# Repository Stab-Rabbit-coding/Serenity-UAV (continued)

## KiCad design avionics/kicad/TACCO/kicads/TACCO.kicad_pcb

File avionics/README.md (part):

# Serenity UAV — Avionics Subsystem

**License:** CC BY-SA 4.0 — creativecommons.org/licenses/by-sa/4.0 (SPDX-License-Identifier: CC-BY-SA-4.0)
see [License](#license) below.  
**Current design revision:** tracked per board, not subsystem-wide — see "PCB Boards" below and
each board's own `avionics/kicad/<board>/<board>.md` status file for its current revision and
sch↔PCB parity state. `avionics/WBS.md` carries the subsystem-wide work breakdown (no changelog
section number is stable enough to cite here; search the file instead of citing a section).

> Avionics subsystem for the Serenity UAV: 8-node cooperative flight control,
> PACE failover architecture, EMI-hardened PCBs, multi-link comms (CAN FD, RS-485,
> Ethernet, MIL-STD-1553C, 49 MHz / SiK / mLRS), and signed telemetry logging with
> hardware-enforced write protection.

## Current Status (2026-10-07)

The design revision is Rev T. Hardware is in PCB layout; nothing is fabricated yet.

| Item | State |
|------|-------|
| Pilot | Schematic and PCB generated together; ERC 0, DRC 0, parity 0; 120 of 120 parts placed; **routing and Gerbers open** |
| TACCO | 163 parts placed on a 60 × 35 mm outline; ERC 0, DRC 0, parity 0 before routing; **routing, Gerbers, and USB Wi-Fi module selection (fab blocker) open** |
| PB2 rails (Pilot, TACCO) | Corrected 2026-10-05/06 to 4.80 mm from each long edge on Samtec TSM-118-04-L-DV-LC male strips; the earlier 2.54 mm placement could not mate with the PB2-I |
| Fleet 1553C | Holt HI-6138 protocol engine on Pilot and TACCO (decision 2026-09-28) |
| Flight Engineer | ERC 0; 29–31 DRC items open; not routed |
| Commo | Rev T standalone bus node approved 2026-09-29; Rev S cape design superseded; Rev T schematic and PCB in design |
| Observer | Schematic ahead of PCB; PCB resync not started (124 DRC) |
| Bus-Gateway | `N_STACKS=4` generated; about 84% routed; 1 DRC item |
| Encoder | Schematic, PCB, ERC 0, DRC 0; bench calibration open |
| Firmware | `serenity-cn` Phase 6 done; `serenity-fc` Phase 6 stub; Phase 7 open (`firmware/WBS.md`) |

Per-board detail: `kicad/README.md` and each board's `.md` file. Open work: `TODO.md`.

## Architecture Overview

**8-Node PACE Failover System** (Primary / Alternative / Contingency / Emergency):

| Stack | Watchdog | Comms | Flight Control | Payload |
|-------|----------|-------|----------------|---------|
| Shepherd (Bay A) | P | A | C | E |
| Inara (Bay B) | A | P | E | C |
| River (Bay C) | C | E | P | A |
| Simon (Bay D) | A | C | A | P |

Each node runs a **PocketBeagle2 Industrial (PB2-I) SBC** carrying:

- **Pilot** cape: flight control + sensor interface (Cape-A-2)
- **TACCO** cape: comms/logging/payload interface (Cape-B-2). "XO" is a legacy/internal working
  name still present in some script and file names (e.g. `gen_xo_sch.py`) — TACCO is the
  canonical current name; see `avionics/AGENTS.md` "Cape Naming and Revision History."
- **Commo** (49 MHz + SiK transceivers). Rev S was a PB2-I cape in River's Room (Bay C) and
  Simon's Medbay (Bay D). **Rev T (approved 2026-09-29)** replaces both with one standalone
  MCU node at the antennas, reachable by all four stacks; see `avionics/AGENTS.md`.

**Flight Engineer** (Power Distribution Board) sits in the middle-section inner neck, minimizing
power-run length to all four nacelles and the battery.

**Observer** (standalone vision/ToF/laser board — not a PB2-I cape) installs at the nose and
cargo-bay mounting sites, connected via the Ethernet ring and CAN FD trunk. It shares the
Ethernet ring with the 8 PACE nodes but is not itself one of them, so the ring's actual physical
node count exceeds 8 — see `avionics/AGENTS.md` and `avionics/kicad/Observer/Observer.md`.

**Bus-Gateway** (CAN-PERIPH-GW-1) is a secure CAN-FD/RS-485 edge node that brings bus connectivity
to sensors/actuators that lack it natively — nacelle tilt Hall-effect encoders, SG90
micro-servos (winch, cargo door), and per-EDF ESC telemetry. It is deployed in multiple physical
instances (per-nacelle encoder gateway, per-EDF ESC gateway, cargo-door servo gateway); see
`avionics/kicad/Bus-Gateway/CAN-PERIPH-GW-1.md`. The Pilot/TACCO README bullets below describe
these signals as if read/driven locally; several have since moved to bus-networked control
through Bus-Gateway — check the per-board `.md` files for current wiring before assuming a
local GPIO/analog connection.

**Encoder** (ENC-NACELLE-1) is the nacelle tilt-angle sensor PCB (AK7455 off-axis magnetoresistive
encoder); it now reports over CAN-FD/RS-485 through Bus-Gateway rather than being read directly
by Pilot — see `avionics/kicad/Encoder/ENC-NACELLE-1.md`.

## Onboard Bus Architecture

| Bus | Protocol | Nodes | Purpose |
|-----|----------|-------|---------|
| CAN FD | 1 Mbps nominal / 8 Mbps data | 8 PACE nodes + Bus-Gateway instances + Observer + Commo (Rev T) + Flight Engineer | Primary telemetry, ESC heartbeat, sensor fusion, failover signaling |
| RS-485 | Half-duplex | 8 PACE nodes + Bus-Gateway instances + Commo (Rev T) + Flight Engineer | Backup command/telemetry (fallback if CAN FD fails) |
| Ethernet | RSTP ring | 8 PACE nodes (via Pilot's dual PHYs, J_ETH1/J_ETH2) + Observer | High-bandwidth sensor data, inter-node video/imaging streams |
| MIL-STD-1553C | Dual redundant buses | 8 PACE nodes + Commo (Rev T) as a remote terminal | Deterministic real-time control; Holt HI-6138 protocol engine on every Pilot and TACCO |
| UART | Various | Cape headers | Serial debugging, bootloader, optional mission-specific sensors |

## External Comms (5 Independent Paths)

All five paths are **authenticated, signed, logged**. Every stack's TACCO cape carries Wi-Fi,
ZigBee, and mLRS. Under Rev S only River and Simon carried a Commo cape (49 MHz + SiK); under
Rev T every stack reaches the one standalone Commo node over the bus. See root `AGENTS.md` §9 for
the per-stack primary/secondary assignment.

1. **Wi-Fi 5 GHz** — MAVLink to QGroundControl; primary for higher-bandwidth development
   flights; range limited (<500 m line-of-sight); all 4 stacks (TACCO). Host interface moved to a
   USB module on the PB2's USB1 (the SDIO bus is not on the PB2 headers); module selection is open
2. **ZigBee 2.4 GHz** — MAVLink fallback; robust link in congested RF environments; all 4 stacks
   (TACCO, Murata Type 2EL module; 802.15.4 is hosted on SPI0)
3. **mLRS (bare ST STM32WLE5JC)** — LoRa-class long-range link; all 4 stacks (TACCO). Replaced
   the Seeed Wio-E5 module on 2026-09-29 (restricted-country sourcing rule); RF matching values
   need bench tuning before flight. Replaced TACCO's SiK radio in the 2026-09-21 relocation and
   is the long-range fallback if the single Commo node is lost
4. **MAVLink/SiK 915 MHz** — Licensed ISM band; range ~5 km (open field, typical line-of-sight);
   via Commo (RFD900ux-SMT) — moved there from TACCO in the 2026-09-21 relocation. Rev S: River
   and Simon only; Rev T: all stacks
5. **49 MHz (Part 15 §15.235)** — Unlicensed, extremely low power (~30 µW EIRP); via Commo (Rev S: River and
   Simon only; Rev T: all stacks); forward and aft wire antennas (see `XCVR-49MHZ` in BOM); carries
   encrypted command/telemetry; requires FCC pre-compliance (energy-limited but not
   power-limited per Part 15)

## PCB Boards

Board revisions, sch↔PCB parity, ERC/DRC status, and exact IC/rail specs move fast and are
tracked at the source — each board's own `avionics/kicad/<board>/<board>.md`, cross-referenced
from `avionics/TODO.md` §1.2. The summaries below are architectural (what the board does, not
its exact current bring-up state); confirm specifics against the per-board `.md` before relying
on them for fab, BOM, or integration decisions.

### Pilot (Cape-A-2) — Flight Control + Sensors

- **Processor:** PocketBeagle2 Industrial (Cortex-A53, dual PRU real-time subsystem)
- **Sensors:** 9-DOF IMU, barometric altimeter, GPS (u-blox M10Q)
- **Motor Control:** 4× PWM outputs (ESC1–4) for nacelle EDFs; isolated gate drivers
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
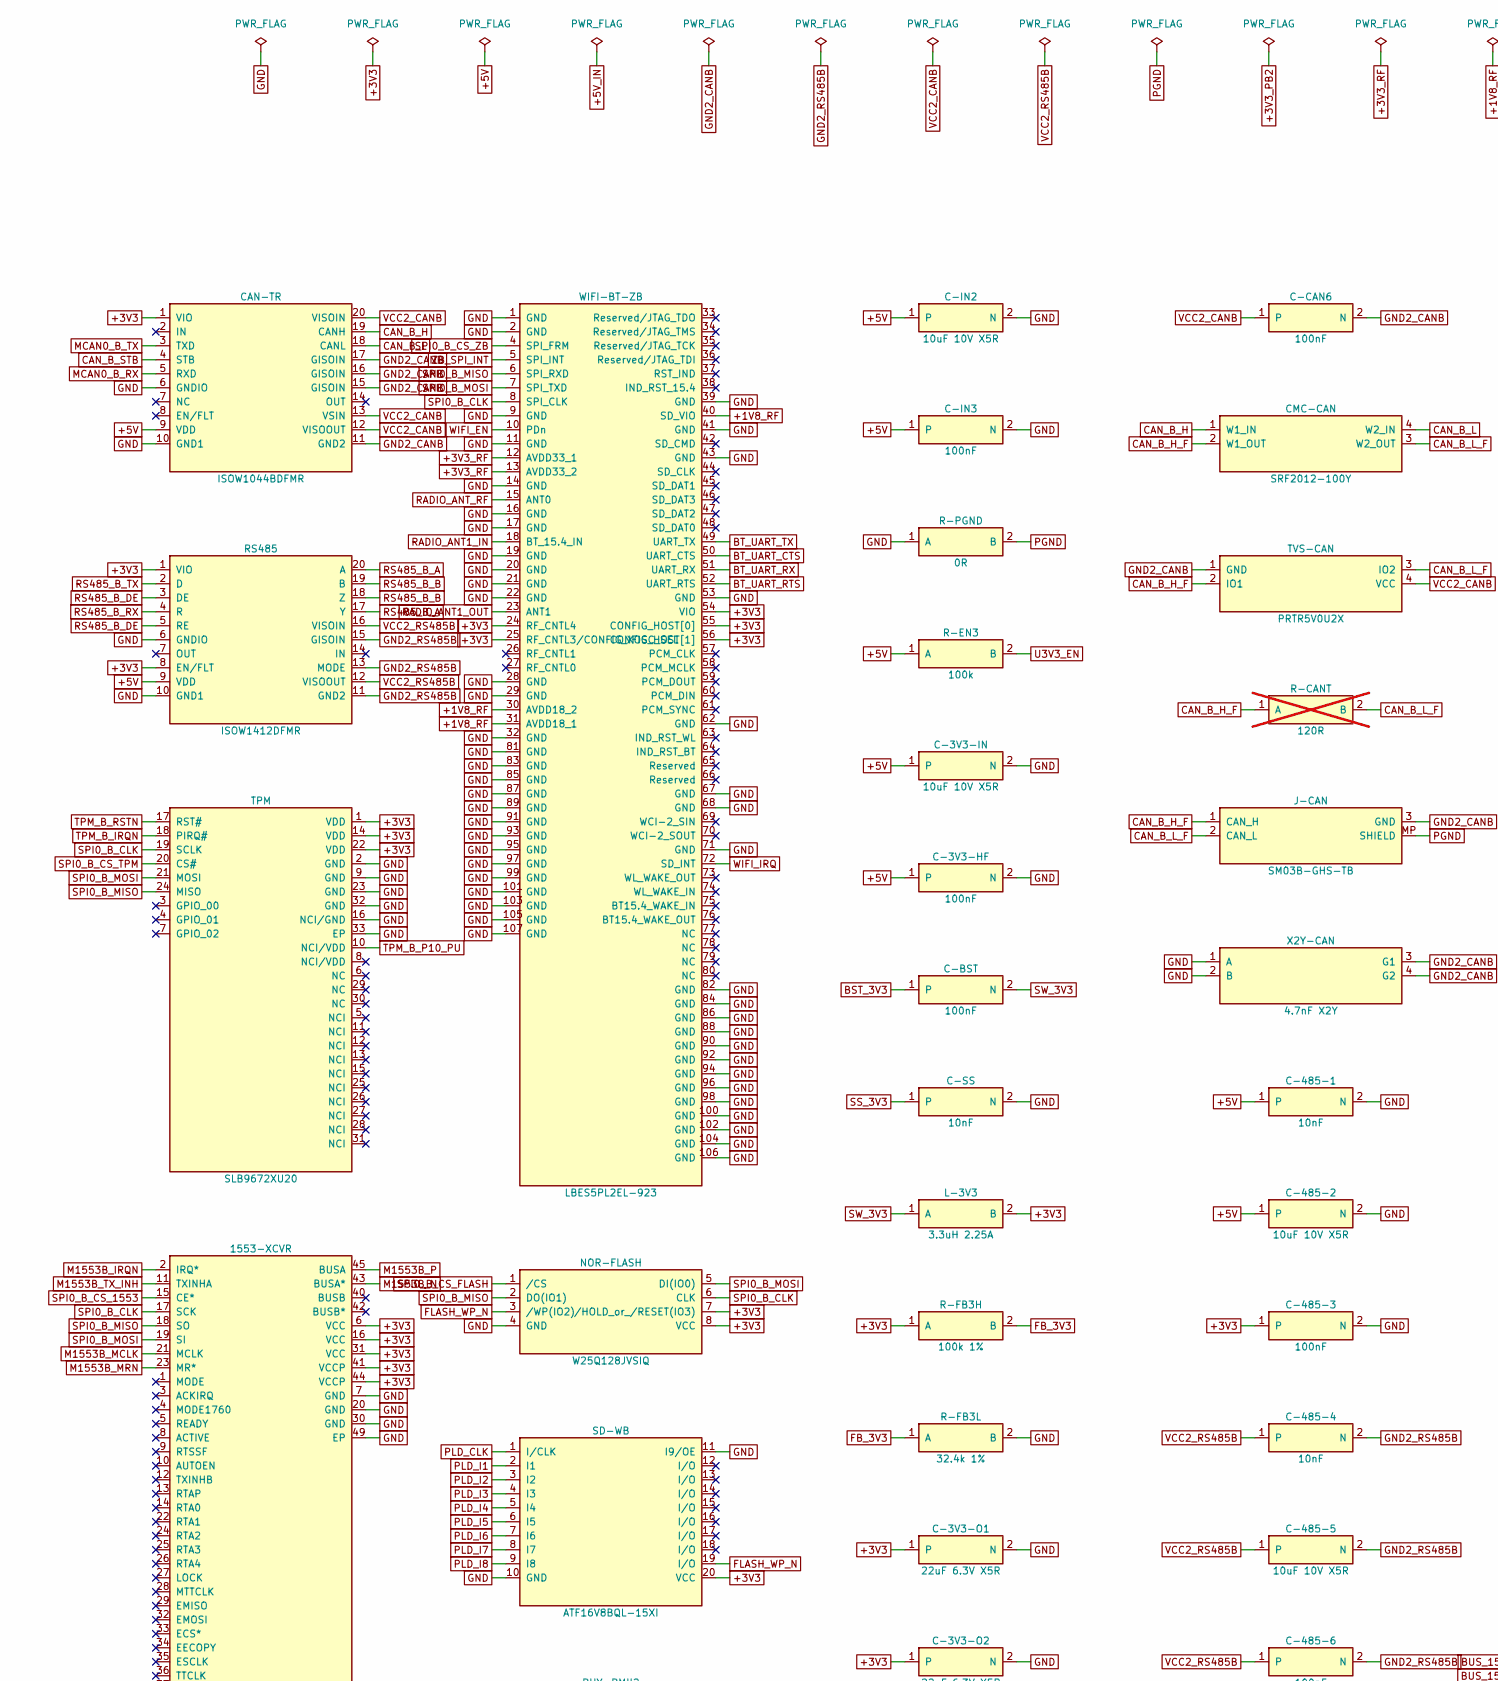
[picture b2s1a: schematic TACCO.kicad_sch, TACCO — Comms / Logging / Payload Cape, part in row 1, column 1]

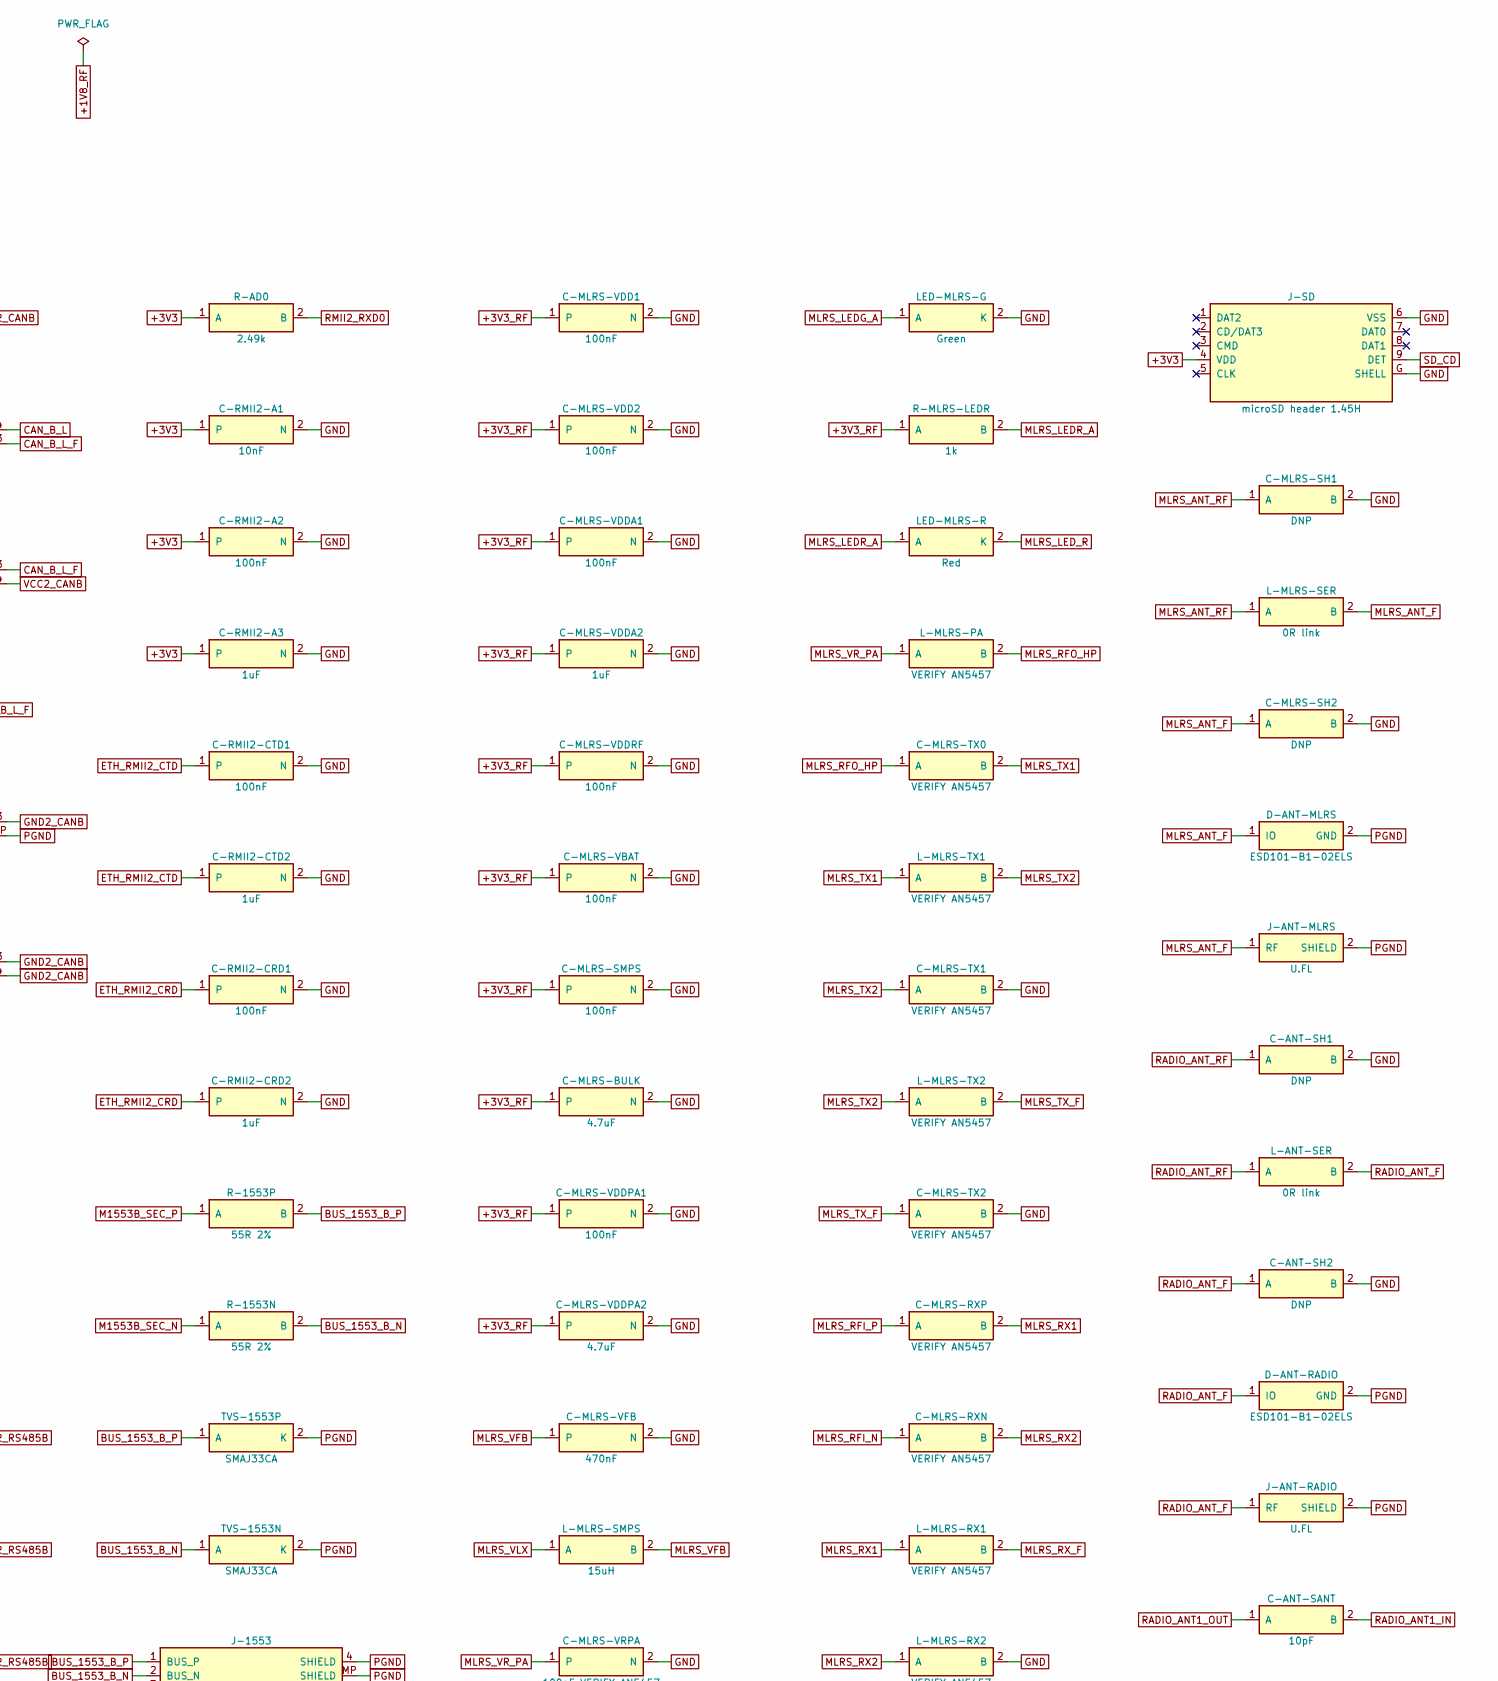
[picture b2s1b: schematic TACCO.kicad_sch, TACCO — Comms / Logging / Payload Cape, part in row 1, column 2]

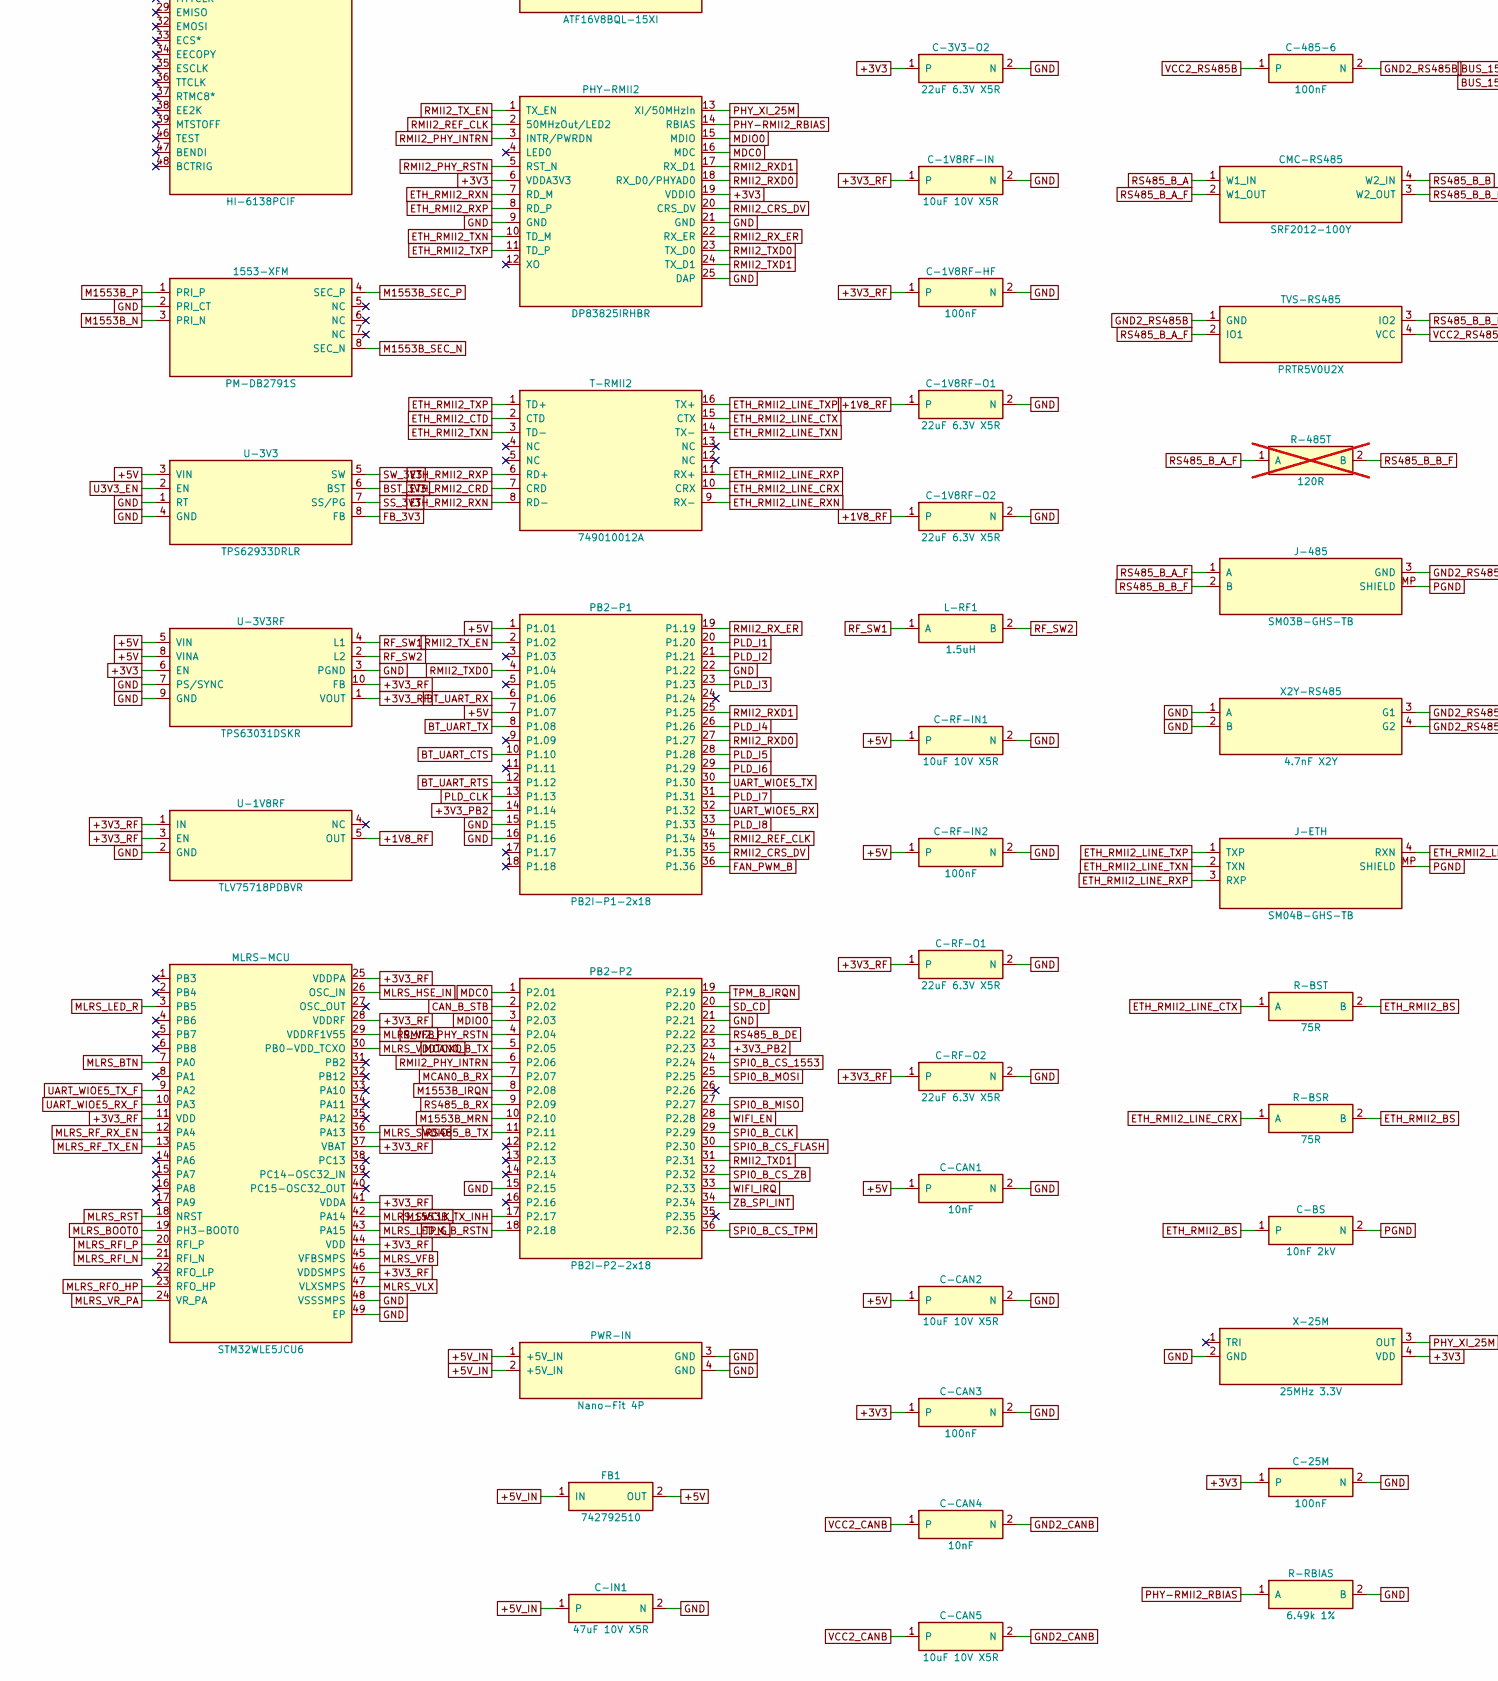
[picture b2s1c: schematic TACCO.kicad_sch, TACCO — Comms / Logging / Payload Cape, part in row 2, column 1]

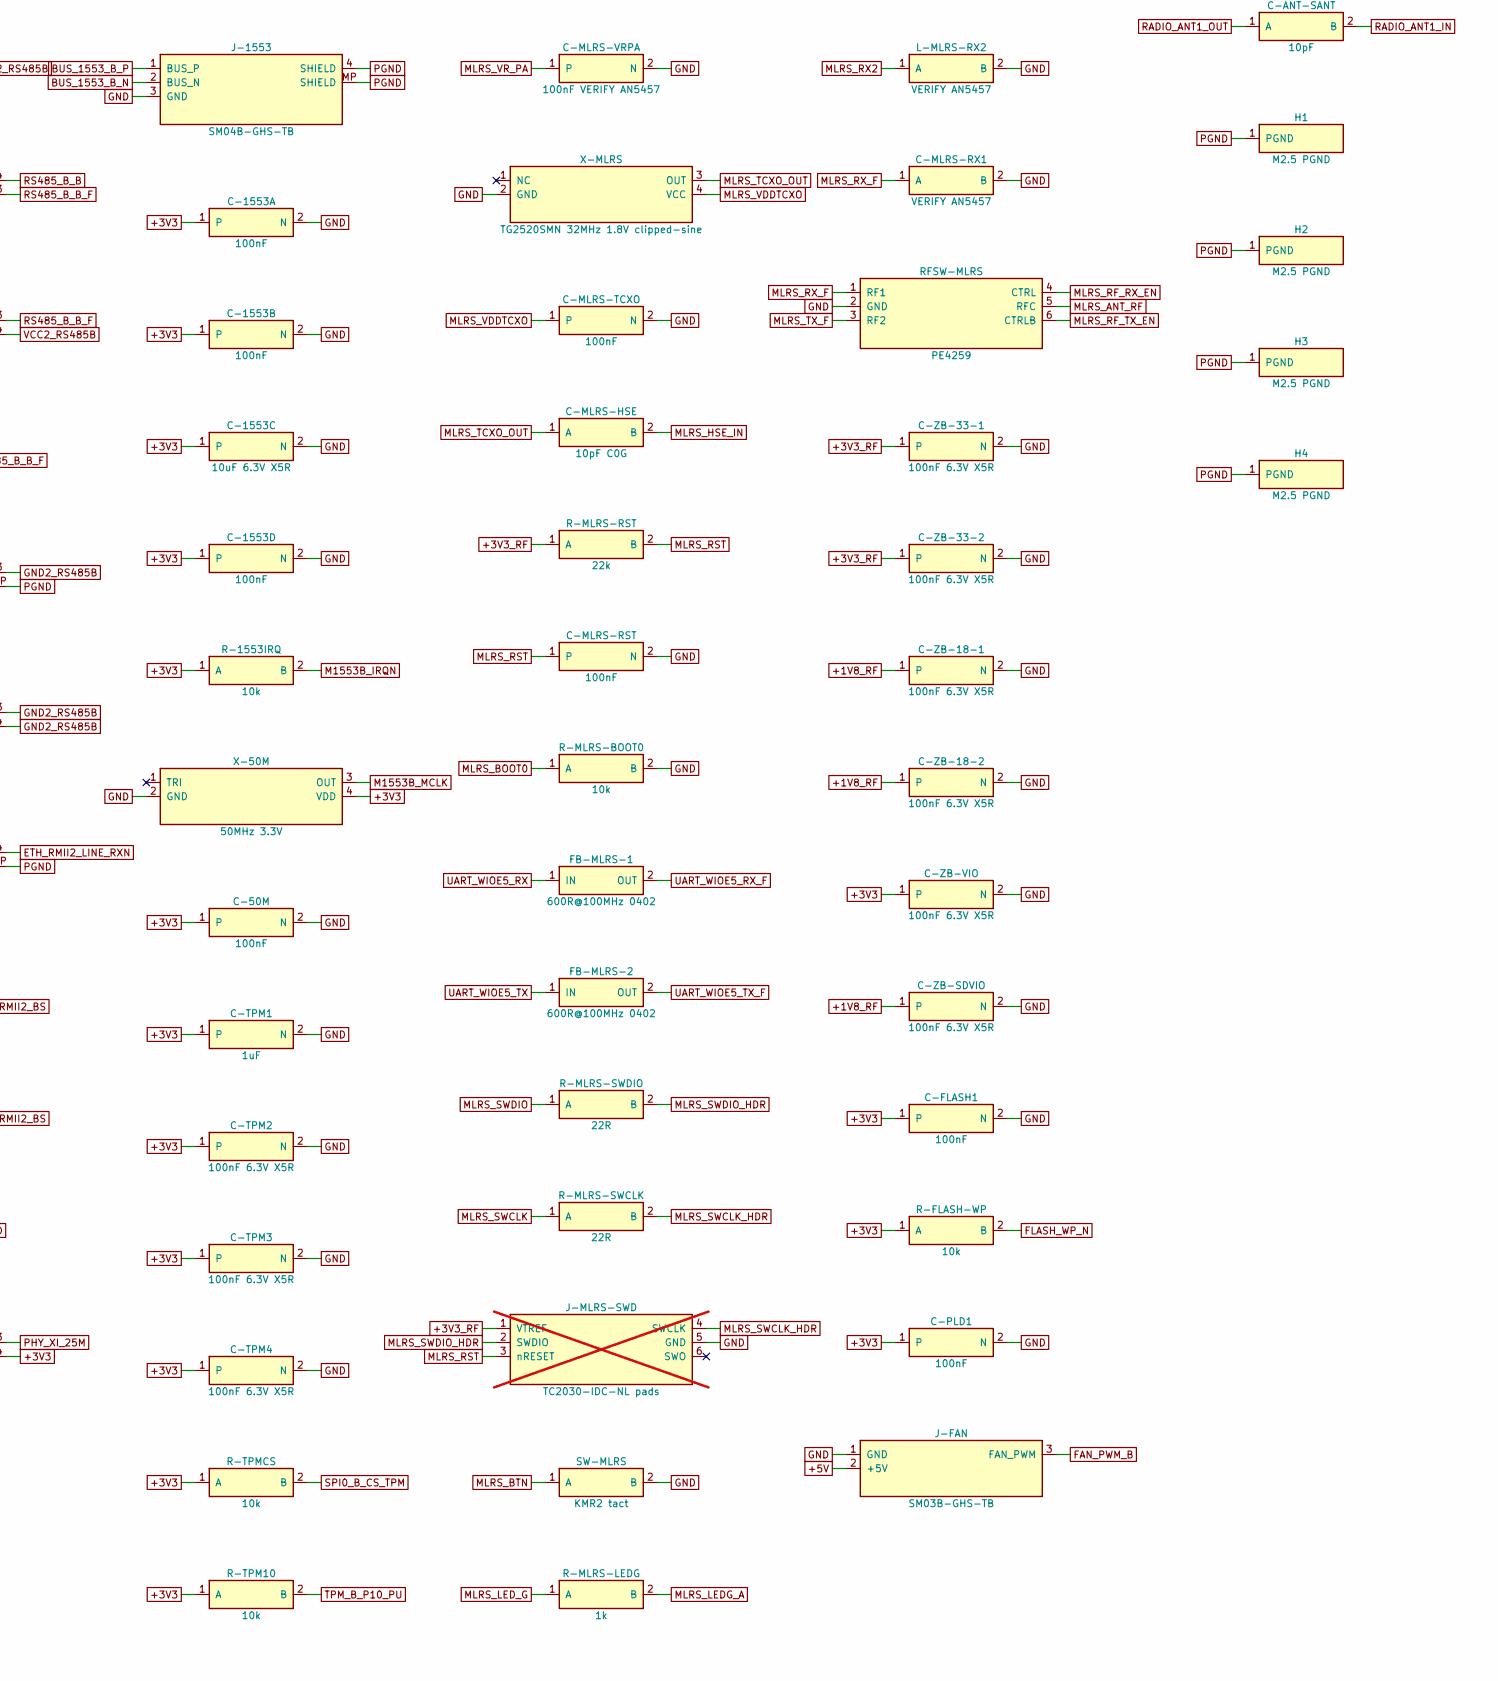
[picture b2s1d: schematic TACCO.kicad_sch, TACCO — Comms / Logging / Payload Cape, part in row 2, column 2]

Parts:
1553-XCVR: HI-6138PCIF; Holt_HI-6138_QFN-48_6x6mm_P0.4mm_EP4.6mm; MPN HI-6138PCIF
1553-XFM: PM-DB2791S; Xfmr_1553_SMD_0.40in_8pin; MPN PM-DB2791S
C-1V8RF-HF, C-3V3-HF, C-25M, C-50M, C-485-3, C-485-6, C-1553A, C-1553B, C-1553D: 100nF; C_0402_1005Metric
C-1V8RF-IN, C-3V3-IN, C-485-2, C-485-5: 10uF 10V X5R; C_0603_1608Metric
C-1V8RF-O1, C-1V8RF-O2, C-3V3-O1, C-3V3-O2: 22uF 6.3V X5R; C_0603_1608Metric
C-485-1, C-485-4: 10nF; C_0201_0603Metric
C-1553C: 10uF 6.3V X5R; C_0603_1608Metric
C-ANT-SANT: 10pF; C_0201_0603Metric
C-ANT-SH1, C-ANT-SH2: DNP; C_0402_1005Metric
C-BS: 10nF 2kV; C_1808_4520Metric
C-BST: 100nF; C_0402_1005Metric
C-CAN1, C-CAN4: 10nF; C_0201_0603Metric
C-CAN2, C-CAN5: 10uF 10V X5R; C_0603_1608Metric
C-CAN3, C-CAN6: 100nF; C_0402_1005Metric
C-FLASH1: 100nF; C_0402_1005Metric
C-IN1: 47uF 10V X5R; C_1210_3225Metric
C-IN2: 10uF 10V X5R; C_0603_1608Metric
C-IN3: 100nF; C_0402_1005Metric
C-MLRS-BULK: 4.7uF; C_0603_1608Metric
C-MLRS-HSE: 10pF C0G; C_0402_1005Metric
C-MLRS-RST: 100nF; C_0402_1005Metric
C-MLRS-RX1: VERIFY AN5457; C_0402_1005Metric
C-MLRS-RXN: VERIFY AN5457; C_0402_1005Metric
C-MLRS-RXP: VERIFY AN5457; C_0402_1005Metric
C-MLRS-SH1, C-MLRS-SH2: DNP; C_0201_0603Metric
C-MLRS-SMPS: 100nF; C_0402_1005Metric
C-MLRS-TCXO: 100nF; C_0402_1005Metric
C-MLRS-TX0, C-MLRS-TX1, C-MLRS-TX2: VERIFY AN5457; C_0402_1005Metric
C-MLRS-VBAT: 100nF; C_0402_1005Metric
C-MLRS-VDD1, C-MLRS-VDD2: 100nF; C_0402_1005Metric
C-MLRS-VDDA1: 100nF; C_0402_1005Metric
C-MLRS-VDDA2: 1uF; C_0402_1005Metric
C-MLRS-VDDPA1: 100nF; C_0402_1005Metric
C-MLRS-VDDPA2: 4.7uF; C_0603_1608Metric
C-MLRS-VDDRF: 100nF; C_0402_1005Metric
C-MLRS-VFB: 470nF; C_0402_1005Metric
C-MLRS-VRPA: 100nF VERIFY AN5457; C_0402_1005Metric
C-PLD1: 100nF; C_0402_1005Metric
C-RF-IN1: 10uF 10V X5R; C_0603_1608Metric
C-RF-IN2: 100nF; C_0402_1005Metric
C-RF-O1, C-RF-O2: 22uF 6.3V X5R; C_0603_1608Metric
C-RMII2-A1: 10nF; C_0201_0603Metric
C-RMII2-A2, C-RMII2-CRD1, C-RMII2-CTD1: 100nF; C_0402_1005Metric
C-RMII2-A3, C-RMII2-CRD2, C-RMII2-CTD2: 1uF; C_0402_1005Metric
C-SS: 10nF; C_0201_0603Metric
C-TPM1: 1uF; C_0402_1005Metric
C-TPM2, C-TPM3, C-TPM4: 100nF 6.3V X5R; C_0201_0603Metric
C-ZB-18-1, C-ZB-18-2, C-ZB-33-1, C-ZB-33-2: 100nF 6.3V X5R; C_0201_0603Metric
C-ZB-SDVIO: 100nF 6.3V X5R; C_0201_0603Metric
C-ZB-VIO: 100nF 6.3V X5R; C_0201_0603Metric
CAN-TR: ISOW1044BDFMR; SOIC-20W_7.5x12.8mm_P1.27mm; MPN ISOW1044BDFMR
CMC-CAN: SRF2012-100Y; Bourns_SRF2012_4T; MPN SRF2012-121YA
CMC-RS485: SRF2012-100Y; Bourns_SRF2012_4T; MPN SRF2012-121YA
D-ANT-MLRS: ESD101-B1-02ELS; Infineon_TSSLP-2-4_0.62x0.32mm; MPN ESD101-B1-02ELS
D-ANT-RADIO: ESD101-B1-02ELS; Infineon_TSSLP-2-4_0.62x0.32mm; MPN ESD101-B1-02ELS
FB1: 742792510; L_1812_4532Metric; MPN 742792510
FB-MLRS-1, FB-MLRS-2: 600R@100MHz 0402; L_0402_1005Metric
H1, H2, H3, H4: M2.5 PGND; MountingHole_2.7mm_M2.5_PGND_Ring
J-485: SM03B-GHS-TB; JST_GH_SM03B-GHS-TB_1x03-1MP_P1.25mm_Horizontal; MPN SM03B-GHS-TB(LF)(SN)
J-1553: SM04B-GHS-TB; JST_GH_SM04B-GHS-TB_1x04-1MP_P1.25mm_Horizontal; MPN SM04B-GHS-TB(LF)(SN)
J-ANT-MLRS: U.FL; U.FL_Hirose_U.FL-R-SMT-1_Vertical; MPN U.FL-R-SMT-1(10)
J-ANT-RADIO: U.FL; U.FL_Hirose_U.FL-R-SMT-1_Vertical; MPN U.FL-R-SMT-1(10)
J-CAN: SM03B-GHS-TB; JST_GH_SM03B-GHS-TB_1x03-1MP_P1.25mm_Horizontal; MPN SM03B-GHS-TB(LF)(SN)
J-ETH: SM04B-GHS-TB; JST_GH_SM04B-GHS-TB_1x04-1MP_P1.25mm_Horizontal; MPN SM04B-GHS-TB(LF)(SN)
J-FAN: SM03B-GHS-TB; JST_GH_SM03B-GHS-TB_1x03-1MP_P1.25mm_Horizontal; MPN SM03B-GHS-TB(LF)(SN)
J-MLRS-SWD: TC2030-IDC-NL pads; Tag-Connect_TC2030-IDC-NL_2x03_P1.27mm_Vertical; not fitted
J-SD: microSD header 1.45H; microSD_Molex_105162-0001; MPN 105162-0001
L-3V3: 3.3uH 2.25A; L_WE-MAPI_3015; MPN 74438335033
L-ANT-SER: 0R link; R_0402_1005Metric
L-MLRS-PA: VERIFY AN5457; L_0402_1005Metric
L-MLRS-RX1, L-MLRS-RX2: VERIFY AN5457; L_0402_1005Metric
L-MLRS-SER: 0R link; R_0402_1005Metric
L-MLRS-SMPS: 15uH; L_0603_1608Metric
L-MLRS-TX1, L-MLRS-TX2: VERIFY AN5457; L_0402_1005Metric
L-RF1: 1.5uH; L_Wuerth_MAPI-3015; MPN LPS3015-152MRC
LED-MLRS-G: Green; LED_0603_1608Metric
LED-MLRS-R: Red; LED_0603_1608Metric
MLRS-MCU: STM32WLE5JCU6; QFN-48-1EP_7x7mm_P0.5mm_EP5.6x5.6mm; MPN STM32WLE5JCU6
NOR-FLASH: W25Q128JVSIQ; SOIC-8_3.9x4.9mm_P1.27mm; MPN W25Q128JVSIQ
PB2-P1: PB2I-P1-2x18; PocketBeagle2_2x18_P1_TSM-DV-LC; MPN TSM-118-04-L-DV-LC
PB2-P2: PB2I-P2-2x18; PocketBeagle2_2x18_P2_TSM-DV-LC; MPN TSM-118-04-L-DV-LC
PHY-RMII2: DP83825IRHBR; Texas_RMQ0024A_WQFN-24-1EP_3x3mm_P0.4mm_EP1.9x1.9mm; MPN DP83825IRHBR
PWR-IN: Nano-Fit 4P; Molex_NanoFit_1x04_Horizontal; MPN 105313-1204
R-485T: 120R; R_0402_1005Metric; not fitted
R-1553IRQ: 10k; R_0402_1005Metric
R-1553N, R-1553P: 55R 2%; R_0603_1608Metric
R-AD0: 2.49k; R_0201_0603Metric
R-BSR: 75R; R_0402_1005Metric
R-BST: 75R; R_0402_1005Metric
R-CANT: 120R; R_0402_1005Metric; not fitted
R-EN3: 100k; R_0201_0603Metric
R-FB3H: 100k 1%; R_0201_0603Metric
R-FB3L: 32.4k 1%; R_0201_0603Metric
R-FLASH-WP: 10k; R_0201_0603Metric
R-MLRS-BOOT0: 10k; R_0201_0603Metric
R-MLRS-LEDG: 1k; R_0201_0603Metric
R-MLRS-LEDR: 1k; R_0201_0603Metric
R-MLRS-RST: 22k; R_0201_0603Metric
R-MLRS-SWCLK: 22R; R_0201_0603Metric
R-MLRS-SWDIO: 22R; R_0201_0603Metric
R-PGND: 0R; R_0805_2012Metric
R-RBIAS: 6.49k 1%; R_0201_0603Metric
R-TPM10: 10k; R_0201_0603Metric
R-TPMCS: 10k; R_0201_0603Metric
RFSW-MLRS: PE4259; SOT-363_SC-70-6; MPN PE4259-63
RS485: ISOW1412DFMR; SOIC-20W_7.5x12.8mm_P1.27mm; MPN ISOW1412DFMR
SD-WB: ATF16V8BQL-15XI; TSSOP-20_4.4x6.5mm_P0.65mm; MPN ATF16V8BQL-15XI
SW-MLRS: KMR2 tact; SW_Push_1P1T_NO_CK_KMR2
T-RMII2: 749010012A; Wurth_749010012A_WE-LAN; MPN 749010012A
TPM: SLB9672XU20; QFN-32-1EP_5x5mm_P0.5mm_EP3.6x3.6mm; MPN SLB9672XU20FW1611XUMA1
TVS-1553N, TVS-1553P: SMAJ33CA; D_SMA; MPN SMAJ33CA
TVS-CAN: PRTR5V0U2X; SOT-143; MPN PRTR5V0U2X,315
TVS-RS485: PRTR5V0U2X; SOT-143; MPN PRTR5V0U2X,315
U-1V8RF: TLV75718PDBVR; SOT-23-5; MPN TLV75718PDBVR
U-3V3: TPS62933DRLR; SOT-583-8; MPN TPS62933DRLR
U-3V3RF: TPS63031DSKR; TPS6303x_VSON-10_2p5; MPN TPS63031DSKR
WIFI-BT-ZB: LBES5PL2EL-923; Murata_Type2EL_LGA107; MPN LBES5PL2EL-923
X2Y-CAN, X2Y-RS485: 4.7nF X2Y; X2Y_0805_4T; MPN CX0805MRX7R0BB472
X-25M: 25MHz 3.3V; Oscillator_SMD_ECS_2520MV-xxx-xx-4Pin_2.5x2.0mm; MPN ECS-2520MV-250-BN-TR
X-50M: 50MHz 3.3V; Oscillator_SMD_ECS_2520MV-xxx-xx-4Pin_2.5x2.0mm; MPN ECS-2520MV-500-BN-TR
X-MLRS: TG2520SMN 32MHz 1.8V clipped-sine; Oscillator_SMD_SeikoEpson_TG2520SMN-xxx-xxxxxx-4Pin_2.5x2.0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

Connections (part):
+1V8_RF: C-1V8RF-O1.1, C-1V8RF-O2.1, C-ZB-18-1.1, C-ZB-18-2.1, C-ZB-SDVIO.1, U-1V8RF.5 (OUT), WIFI-BT-ZB.30 (AVDD18_2), WIFI-BT-ZB.31 (AVDD18_1), WIFI-BT-ZB.40 (SD_VIO)
+3V3: 1553-XCVR.6 (VCC), 1553-XCVR.16 (VCC), 1553-XCVR.31 (VCC), 1553-XCVR.41 (VCCP), 1553-XCVR.44 (VCCP), C-3V3-O1.1, C-3V3-O2.1, C-25M.1, C-50M.1, C-485-3.1, C-1553A.1, C-1553B.1, C-1553C.1, C-1553D.1, C-CAN3.1, C-FLASH1.1, C-PLD1.1, C-RMII2-A1.1, C-RMII2-A2.1, C-RMII2-A3.1, C-TPM1.1, C-TPM2.1, C-TPM3.1, C-TPM4.1, C-ZB-VIO.1, CAN-TR.1 (VIO), J-SD.4 (VDD), L-3V3.2 (B), NOR-FLASH.7 (/HOLD_or_/RESET(IO3)), NOR-FLASH.8 (VCC), PHY-RMII2.6 (VDDA3V3), PHY-RMII2.19 (VDDIO), R-1553IRQ.1 (A), R-AD0.1 (A), R-FB3H.1 (A), R-FLASH-WP.1 (A), R-TPM10.1 (A), R-TPMCS.1 (A), RS485.1 (VIO), RS485.8 (EN/FLT), SD-WB.20 (VCC), TPM.1 (VDD), TPM.14 (VDD), TPM.22 (VDD), U-3V3RF.6 (EN), WIFI-BT-ZB.24 (RF_CNTL4), WIFI-BT-ZB.25 (RF_CNTL3/CONFIG_XOSC_SEL), WIFI-BT-ZB.54 (VIO), WIFI-BT-ZB.55 (CONFIG_HOST[0]), WIFI-BT-ZB.56 (CONFIG_HOST[1]), X-25M.4 (VDD), X-50M.4 (VDD)
+3V3_PB2: PB2-P1.14 (P1.14), PB2-P2.23 (P2.23)
+3V3_RF: C-1V8RF-HF.1, C-1V8RF-IN.1, C-MLRS-BULK.1, C-MLRS-SMPS.1, C-MLRS-VBAT.1, C-MLRS-VDD1.1, C-MLRS-VDD2.1, C-MLRS-VDDA1.1, C-MLRS-VDDA2.1, C-MLRS-VDDPA1.1, C-MLRS-VDDPA2.1, C-MLRS-VDDRF.1, C-RF-O1.1, C-RF-O2.1, C-ZB-33-1.1, C-ZB-33-2.1, J-MLRS-SWD.1 (VTREF), MLRS-MCU.11 (VDD), MLRS-MCU.25 (VDDPA), MLRS-MCU.28 (VDDRF), MLRS-MCU.37 (VBAT), MLRS-MCU.41 (VDDA), MLRS-MCU.44 (VDD), MLRS-MCU.46 (VDDSMPS), R-MLRS-LEDR.1 (A), R-MLRS-RST.1 (A), U-1V8RF.1 (IN), U-1V8RF.3 (EN), U-3V3RF.1 (VOUT), U-3V3RF.10 (FB), WIFI-BT-ZB.12 (AVDD33_1), WIFI-BT-ZB.13 (AVDD33_2)
+5V: C-3V3-HF.1, C-3V3-IN.1, C-485-1.1, C-485-2.1, C-CAN1.1, C-CAN2.1, C-IN2.1, C-IN3.1, C-RF-IN1.1, C-RF-IN2.1, CAN-TR.9 (VDD), FB1.2 (OUT), J-FAN.2 (+5V), PB2-P1.1 (P1.01), PB2-P1.7 (P1.07), R-EN3.1 (A), RS485.9 (VDD), U-3V3.3 (VIN), U-3V3RF.5 (VIN), U-3V3RF.8 (VINA)
+5V_IN: C-IN1.1, FB1.1 (IN), PWR-IN.1 (+5V_IN), PWR-IN.2 (+5V_IN)
BST_3V3: C-BST.1, U-3V3.6 (BST)
BT_UART_CTS: PB2-P1.10 (P1.10), WIFI-BT-ZB.50 (UART_CTS)
BT_UART_RTS: PB2-P1.12 (P1.12), WIFI-BT-ZB.52 (UART_RTS)
BT_UART_RX: PB2-P1.6 (P1.06), WIFI-BT-ZB.51 (UART_RX)
BT_UART_TX: PB2-P1.8 (P1.08), WIFI-BT-ZB.49 (UART_TX)
BUS_1553_B_N: J-1553.2 (BUS_N), R-1553N.2 (B), TVS-1553N.1 (A)
BUS_1553_B_P: J-1553.1 (BUS_P), R-1553P.2 (B), TVS-1553P.1 (A)
CAN_B_H: CAN-TR.19 (CANH), CMC-CAN.1 (W1_IN)
CAN_B_H_F: CMC-CAN.2 (W1_OUT), J-CAN.1 (CAN_H), R-CANT.1 (A), TVS-CAN.2 (IO1)
CAN_B_L: CAN-TR.18 (CANL), CMC-CAN.4 (W2_IN)
CAN_B_L_F: CMC-CAN.3 (W2_OUT), J-CAN.2 (CAN_L), R-CANT.2 (B), TVS-CAN.3 (IO2)
CAN_B_STB: CAN-TR.4 (STB), PB2-P2.2 (P2.02)
ETH_RMII2_BS: C-BS.1, R-BSR.2 (B), R-BST.2 (B)
ETH_RMII2_CRD: C-RMII2-CRD1.1, C-RMII2-CRD2.1, T-RMII2.7 (CRD)
ETH_RMII2_CTD: C-RMII2-CTD1.1, C-RMII2-CTD2.1, T-RMII2.2 (CTD)
ETH_RMII2_LINE_CRX: R-BSR.1 (A), T-RMII2.10 (CRX)
ETH_RMII2_LINE_CTX: R-BST.1 (A), T-RMII2.15 (CTX)
ETH_RMII2_LINE_RXN: J-ETH.4 (RXN), T-RMII2.9 (RX-)
ETH_RMII2_LINE_RXP: J-ETH.3 (RXP), T-RMII2.11 (RX+)
ETH_RMII2_LINE_TXN: J-ETH.2 (TXN), T-RMII2.14 (TX-)
ETH_RMII2_LINE_TXP: J-ETH.1 (TXP), T-RMII2.16 (TX+)
ETH_RMII2_RXN: PHY-RMII2.7 (RD_M), T-RMII2.8 (RD-)
ETH_RMII2_RXP: PHY-RMII2.8 (RD_P), T-RMII2.6 (RD+)
ETH_RMII2_TXN: PHY-RMII2.10 (TD_M), T-RMII2.3 (TD-)
ETH_RMII2_TXP: PHY-RMII2.11 (TD_P), T-RMII2.1 (TD+)
FAN_PWM_B: J-FAN.3 (FAN_PWM), PB2-P1.36 (P1.36)
FB_3V3: R-FB3H.2 (B), R-FB3L.1 (A), U-3V3.8 (FB)
FLASH_WP_N: NOR-FLASH.3 (/WP(IO2)), R-FLASH-WP.2 (B), SD-WB.19 (I/O)
GND: 1553-XCVR.7 (GND), 1553-XCVR.20 (GND), 1553-XCVR.30 (GND), 1553-XCVR.49 (EP), 1553-XFM.2 (PRI_CT), C-1V8RF-HF.2 (N), C-1V8RF-IN.2 (N), C-1V8RF-O1.2 (N), C-1V8RF-O2.2 (N), C-3V3-HF.2 (N), C-3V3-IN.2 (N), C-3V3-O1.2 (N), C-3V3-O2.2 (N), C-25M.2 (N), C-50M.2 (N), C-485-1.2 (N), C-485-2.2 (N), C-485-3.2 (N), C-1553A.2 (N), C-1553B.2 (N), C-1553C.2 (N), C-1553D.2 (N), C-ANT-SH1.2 (B), C-ANT-SH2.2 (B), C-CAN1.2 (N), C-CAN2.2 (N), C-CAN3.2 (N), C-FLASH1.2 (N), C-IN1.2 (N), C-IN2.2 (N), C-IN3.2 (N), C-MLRS-BULK.2 (N), C-MLRS-RST.2 (N), C-MLRS-RX1.2 (B), C-MLRS-SH1.2 (B), C-MLRS-SH2.2 (B), C-MLRS-SMPS.2 (N), C-MLRS-TCXO.2 (N), C-MLRS-TX1.2 (B), C-MLRS-TX2.2 (B), C-MLRS-VBAT.2 (N), C-MLRS-VDD1.2 (N), C-MLRS-VDD2.2 (N), C-MLRS-VDDA1.2 (N), C-MLRS-VDDA2.2 (N), C-MLRS-VDDPA1.2 (N), C-MLRS-VDDPA2.2 (N), C-MLRS-VDDRF.2 (N), C-MLRS-VFB.2 (N), C-MLRS-VRPA.2 (N), C-PLD1.2 (N), C-RF-IN1.2 (N), C-RF-IN2.2 (N), C-RF-O1.2 (N), C-RF-O2.2 (N), C-RMII2-A1.2 (N), C-RMII2-A2.2 (N), C-RMII2-A3.2 (N), C-RMII2-CRD1.2 (N), C-RMII2-CRD2.2 (N), C-RMII2-CTD1.2 (N), C-RMII2-CTD2.2 (N), C-SS.2 (N), C-TPM1.2 (N), C-TPM2.2 (N), C-TPM3.2 (N), C-TPM4.2 (N), C-ZB-18-1.2 (N), C-ZB-18-2.2 (N), C-ZB-33-1.2 (N), C-ZB-33-2.2 (N), C-ZB-SDVIO.2 (N), C-ZB-VIO.2 (N), CAN-TR.6 (GNDIO), CAN-TR.10 (GND1), J-1553.3 (GND), J-FAN.1 (GND), J-MLRS-SWD.5 (GND), J-SD.6 (VSS), J-SD.G (SHELL)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
GND2_CANB: C-CAN4.2 (N), C-CAN5.2 (N), C-CAN6.2 (N), CAN-TR.11 (GND2), CAN-TR.15 (GISOIN), CAN-TR.16 (GISOIN), CAN-TR.17 (GISOIN), J-CAN.3 (GND), TVS-CAN.1 (GND), X2Y-CAN.3 (G1), X2Y-CAN.4 (G2)
GND2_RS485B: C-485-4.2 (N), C-485-5.2 (N), C-485-6.2 (N), J-485.3 (GND), RS485.11 (GND2), RS485.13 (MODE), RS485.15 (GISOIN), TVS-RS485.1 (GND), X2Y-RS485.3 (G1), X2Y-RS485.4 (G2)
M1553B_IRQN: 1553-XCVR.2 (IRQ*), PB2-P2.8 (P2.08), R-1553IRQ.2 (B)
M1553B_MCLK: 1553-XCVR.21 (MCLK), X-50M.3 (OUT)
M1553B_MRN: 1553-XCVR.23 (MR*), PB2-P2.10 (P2.10)
M1553B_N: 1553-XCVR.43 (BUSA*), 1553-XFM.3 (PRI_N)
M1553B_P: 1553-XCVR.45 (BUSA), 1553-XFM.1 (PRI_P)
M1553B_SEC_N: 1553-XFM.8 (SEC_N), R-1553N.1 (A)
M1553B_SEC_P: 1553-XFM.4 (SEC_P), R-1553P.1 (A)
M1553B_TX_INH: 1553-XCVR.11 (TXINHA), PB2-P2.17 (P2.17)
MCAN0_B_RX: CAN-TR.5 (RXD), PB2-P2.7 (P2.07)
MCAN0_B_TX: CAN-TR.3 (TXD), PB2-P2.5 (P2.05)
MDC0: PB2-P2.1 (P2.01), PHY-RMII2.16 (MDC)
MDIO0: PB2-P2.3 (P2.03), PHY-RMII2.15 (MDIO)
MLRS_ANT_F: C-MLRS-SH2.1 (A), D-ANT-MLRS.1 (IO), J-ANT-MLRS.1 (RF), L-MLRS-SER.2 (B)
MLRS_ANT_RF: C-MLRS-SH1.1 (A), L-MLRS-SER.1 (A), RFSW-MLRS.5 (RFC)
MLRS_BOOT0: MLRS-MCU.19 (PH3-BOOT0), R-MLRS-BOOT0.1 (A)
MLRS_BTN: MLRS-MCU.7 (PA0), SW-MLRS.1 (A)
MLRS_HSE_IN: C-MLRS-HSE.2 (B), MLRS-MCU.26 (OSC_IN)
MLRS_LEDG_A: LED-MLRS-G.1 (A), R-MLRS-LEDG.2 (B)
MLRS_LEDR_A: LED-MLRS-R.1 (A), R-MLRS-LEDR.2 (B)
MLRS_LED_G: MLRS-MCU.43 (PA15), R-MLRS-LEDG.1 (A)
MLRS_LED_R: LED-MLRS-R.2 (K), MLRS-MCU.3 (PB5)
MLRS_RFI_N: C-MLRS-RXN.1 (A), MLRS-MCU.21 (RFI_N)
MLRS_RFI_P: C-MLRS-RXP.1 (A), MLRS-MCU.20 (RFI_P)
MLRS_RFO_HP: C-MLRS-TX0.1 (A), L-MLRS-PA.2 (B), MLRS-MCU.23 (RFO_HP)
MLRS_RF_RX_EN: MLRS-MCU.12 (PA4), RFSW-MLRS.4 (CTRL)
MLRS_RF_TX_EN: MLRS-MCU.13 (PA5), RFSW-MLRS.6 (CTRLB)
MLRS_RST: C-MLRS-RST.1, J-MLRS-SWD.3 (nRESET), MLRS-MCU.18 (NRST), R-MLRS-RST.2 (B)
MLRS_RX1: C-MLRS-RXP.2 (B), L-MLRS-RX1.1 (A)
MLRS_RX2: C-MLRS-RXN.2 (B), L-MLRS-RX2.1 (A)
MLRS_RX_F: C-MLRS-RX1.1 (A), L-MLRS-RX1.2 (B), RFSW-MLRS.1 (RF1)
MLRS_SWCLK: MLRS-MCU.42 (PA14), R-MLRS-SWCLK.1 (A)
MLRS_SWCLK_HDR: J-MLRS-SWD.4 (SWCLK), R-MLRS-SWCLK.2 (B)
MLRS_SWDIO: MLRS-MCU.36 (PA13), R-MLRS-SWDIO.1 (A)
MLRS_SWDIO_HDR: J-MLRS-SWD.2 (SWDIO), R-MLRS-SWDIO.2 (B)
MLRS_TCXO_OUT: C-MLRS-HSE.1 (A), X-MLRS.3 (OUT)
MLRS_TX1: C-MLRS-TX0.2 (B), L-MLRS-TX1.1 (A)
MLRS_TX2: C-MLRS-TX1.1 (A), L-MLRS-TX1.2 (B), L-MLRS-TX2.1 (A)
MLRS_TX_F: C-MLRS-TX2.1 (A), L-MLRS-TX2.2 (B), RFSW-MLRS.3 (RF2)
MLRS_VDDTCXO: C-MLRS-TCXO.1, MLRS-MCU.30 (PB0-VDD_TCXO), X-MLRS.4 (VCC)
MLRS_VFB: C-MLRS-VFB.1, L-MLRS-SMPS.2 (B), MLRS-MCU.29 (VDDRF1V55), MLRS-MCU.45 (VFBSMPS)
MLRS_VLX: L-MLRS-SMPS.1 (A), MLRS-MCU.47 (VLXSMPS)
MLRS_VR_PA: C-MLRS-VRPA.1, L-MLRS-PA.1 (A), MLRS-MCU.24 (VR_PA)
PGND: C-BS.2 (N), D-ANT-MLRS.2 (GND), D-ANT-RADIO.2 (GND), H1.1, H2.1, H3.1, H4.1, J-485.MP (SHIELD), J-1553.4 (SHIELD), J-1553.MP (SHIELD), J-ANT-MLRS.2 (SHIELD), J-ANT-RADIO.2 (SHIELD), J-CAN.MP (SHIELD), J-ETH.MP (SHIELD), R-PGND.2 (B), TVS-1553N.2 (K), TVS-1553P.2 (K)
PHY-RMII2_RBIAS: PHY-RMII2.14 (RBIAS), R-RBIAS.1 (A)
PHY_XI_25M: PHY-RMII2.13 (XI/50MHzIn), X-25M.3 (OUT)
PLD_CLK: PB2-P1.13 (P1.13), SD-WB.1 (I/CLK)
PLD_I1: PB2-P1.20 (P1.20), SD-WB.2 (I1)
PLD_I2: PB2-P1.21 (P1.21), SD-WB.3 (I2)
PLD_I3: PB2-P1.23 (P1.23), SD-WB.4 (I3)
PLD_I4: PB2-P1.26 (P1.26), SD-WB.5 (I4)
PLD_I5: PB2-P1.28 (P1.28), SD-WB.6 (I5)
PLD_I6: PB2-P1.29 (P1.29), SD-WB.7 (I6)
PLD_I7: PB2-P1.31 (P1.31), SD-WB.8 (I7)
PLD_I8: PB2-P1.33 (P1.33), SD-WB.9 (I8)
RADIO_ANT1_IN: C-ANT-SANT.2 (B), WIFI-BT-ZB.18 (BT_15.4_IN)
RADIO_ANT1_OUT: C-ANT-SANT.1 (A), WIFI-BT-ZB.23 (ANT1)
RADIO_ANT_F: C-ANT-SH2.1 (A), D-ANT-RADIO.1 (IO), J-ANT-RADIO.1 (RF), L-ANT-SER.2 (B)
RADIO_ANT_RF: C-ANT-SH1.1 (A), L-ANT-SER.1 (A), WIFI-BT-ZB.15 (ANT0)
RF_SW1: L-RF1.1 (A), U-3V3RF.4 (L1)
RF_SW2: L-RF1.2 (B), U-3V3RF.2 (L2)
RMII2_CRS_DV: PB2-P1.35 (P1.35), PHY-RMII2.20 (CRS_DV)
RMII2_PHY_INTRN: PB2-P2.6 (P2.06), PHY-RMII2.3 (INTR/PWRDN)
RMII2_PHY_RSTN: PB2-P2.4 (P2.04), PHY-RMII2.5 (RST_N)
RMII2_REF_CLK: PB2-P1.34 (P1.34), PHY-RMII2.2 (50MHzOut/LED2)
RMII2_RXD0: PB2-P1.27 (P1.27), PHY-RMII2.18 (RX_D0/PHYAD0), R-AD0.2 (B)
RMII2_RXD1: PB2-P1.25 (P1.25), PHY-RMII2.17 (RX_D1)
RMII2_RX_ER: PB2-P1.19 (P1.19), PHY-RMII2.22 (RX_ER)
RMII2_TXD0: PB2-P1.4 (P1.04), PHY-RMII2.23 (TX_D0)
RMII2_TXD1: PB2-P2.31 (P2.31), PHY-RMII2.24 (TX_D1)
RMII2_TX_EN: PB2-P1.2 (P1.02), PHY-RMII2.1 (TX_EN)
RS485_B_A: CMC-RS485.1 (W1_IN), RS485.17 (Y), RS485.20 (A)
RS485_B_A_F: CMC-RS485.2 (W1_OUT), J-485.1 (A), R-485T.1 (A), TVS-RS485.2 (IO1)
RS485_B_B: CMC-RS485.4 (W2_IN), RS485.18 (Z), RS485.19 (B)
RS485_B_B_F: CMC-RS485.3 (W2_OUT), J-485.2 (B), R-485T.2 (B), TVS-RS485.3 (IO2)
RS485_B_DE: PB2-P2.22 (P2.22), RS485.3 (DE), RS485.5 (RE)
RS485_B_RX: PB2-P2.9 (P2.09), RS485.4 (R)
RS485_B_TX: PB2-P2.11 (P2.11), RS485.2 (D)
SD_CD: J-SD.9 (DET), PB2-P2.20 (P2.20)
SPI0_B_CLK: 1553-XCVR.17 (SCK), NOR-FLASH.6 (CLK), PB2-P2.29 (P2.29), TPM.19 (SCLK), WIFI-BT-ZB.8 (SPI_CLK)
SPI0_B_CS_1553: 1553-XCVR.15 (CE*), PB2-P2.24 (P2.24)
SPI0_B_CS_FLASH: NOR-FLASH.1 (/CS), PB2-P2.30 (P2.30)
SPI0_B_CS_TPM: PB2-P2.36 (P2.36), R-TPMCS.2 (B), TPM.20 (CS#)
SPI0_B_CS_ZB: PB2-P2.32 (P2.32), WIFI-BT-ZB.4 (SPI_FRM)
SPI0_B_MISO: 1553-XCVR.18 (SO), NOR-FLASH.2 (DO(IO1)), PB2-P2.27 (P2.27), TPM.24 (MISO), WIFI-BT-ZB.6 (SPI_RXD)
SPI0_B_MOSI: 1553-XCVR.19 (SI), NOR-FLASH.5 (DI(IO0)), PB2-P2.25 (P2.25), TPM.21 (MOSI), WIFI-BT-ZB.7 (SPI_TXD)
SS_3V3: C-SS.1, U-3V3.7 (SS/PG)
SW_3V3: C-BST.2 (N), L-3V3.1 (A), U-3V3.5 (SW)
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
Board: 6 copper layers, 163 parts (68 on the bottom side), 137 nets, no tracks yet.
